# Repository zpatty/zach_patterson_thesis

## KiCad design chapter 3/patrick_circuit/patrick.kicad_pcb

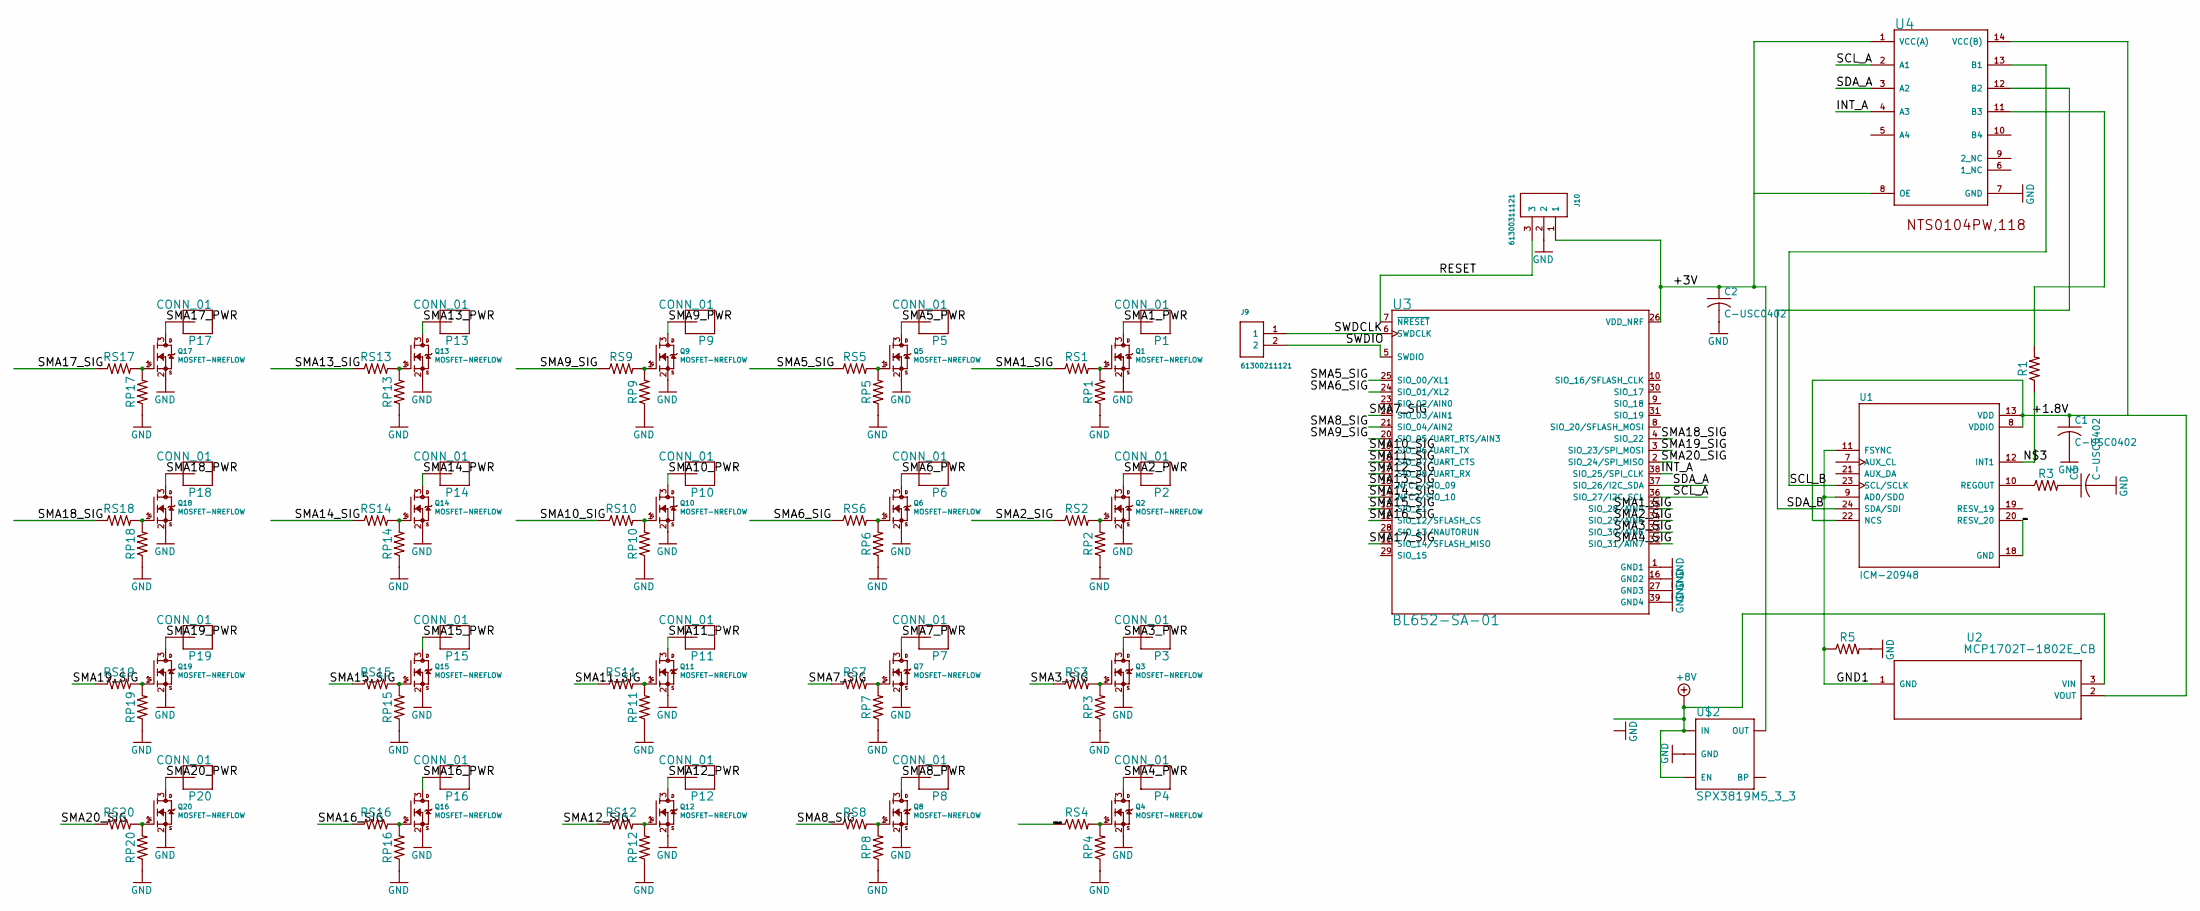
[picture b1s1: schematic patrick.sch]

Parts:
C1, C2, C3: C-USC0402; C0402
J9: 61300211121
J10: 61300311121
P1, P2, P3, P4, P5, P6, P7, P8, P9, P10, P11, P12, P13, P14, P15, P16, P17, P18, P19, P20: CONN_01; 1X01
Q1, Q2, Q3, Q4, Q5, Q6, Q7, Q8, Q9, Q10, Q11, Q12, Q13, Q14, Q15, Q16, Q17, Q18, Q19, Q20: MOSFET-NREFLOW; SOT23
R1, R3, R5: 0805
RP1, RP2, RP3, RP4, RP5, RP6, RP7, RP8, RP9, RP10, RP11, RP12, RP13, RP14, RP15, RP16, RP17, RP18, RP19, RP20: 0402
RS1, RS2, RS3, RS4, RS5, RS6, RS7, RS8, RS9, RS10, RS11, RS12, RS13, RS14, RS15, RS16, RS17, RS18, RS19, RS20: 0402
U1: ICM-20948; QFN40P300X300X105-24N
U2: MCP1702T-1802E_CB; SOT-23A_MC
U3: BL652-SA-01; XCVR_BL652-SA-01
U4: NXP_NTS0104PW,118NXP_NTS0104PW,118_0_3; NXP_NTS0104PW,118_3
U$2: SPX3819M5_3_3; SOT23-5

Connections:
+8V: U2.3 (VIN), U$2.1 (IN), U$2.3 (EN)
/+1.8V: C1.1, U1.8 (VDDIO), U1.13 (VDD), U1.22 (NCS), U2.2 (VOUT), U4.14 (VCC(B))
/+3V: C2.1, J10.1, U3.26 (VDD_NRF), U4.1 (VCC(A)), U4.8 (OE), U$2.5 (OUT)
/GND1: R5.1, U1.9 (AD0/SDO), U1.11 (FSYNC), U1.18 (GND), U1.20 (RESV_20), U2.1 (GND)
/INT_A: U3.38 (SIO_25/SPI_CLK), U4.4 (A3)
/N$3: R1.1, U1.12 (INT1)
/RESET: J10.3, U3.7 (~NRESET)
/SCL_A: U3.36 (SIO_27/I2C_SCL), U4.2 (A1)
/SCL_B: U1.23 (SCL/SCLK), U4.13 (B1)
/SDA_A: U3.37 (SIO_26/I2C_SDA), U4.3 (A2)
/SDA_B: U1.24 (SDA/SDI), U4.12 (B2)
/SMA1_PWR: P1.1, Q1.3 (D)
/SMA1_SIG: RS1.1, U3.35 (SIO_28/AIN4)
/SMA2_PWR: P2.1, Q2.3 (D)
/SMA2_SIG: RS2.1, U3.34 (SIO_29/AIN5)
/SMA3_PWR: P3.1, Q3.3 (D)
/SMA3_SIG: RS3.1, U3.33 (SIO_30/AIN6)
/SMA4_PWR: P4.1, Q4.3 (D)
/SMA4_SIG: RS4.1, U3.32 (SIO_31/AIN7)
/SMA5_PWR: P5.1, Q5.3 (D)
/SMA5_SIG: RS5.1, U3.25 (SIO_00/XL1)
/SMA6_PWR: P6.1, Q6.3 (D)
/SMA6_SIG: RS6.1, U3.24 (SIO_01/XL2)
/SMA7_PWR: P7.1, Q7.3 (D)
/SMA7_SIG: RS7.1, U3.22 (SIO_03/AIN1)
/SMA8_PWR: P8.1, Q8.3 (D)
/SMA8_SIG: RS8.1, U3.21 (SIO_04/AIN2)
/SMA9_PWR: P9.1, Q9.3 (D)
/SMA9_SIG: RS9.1, U3.20 (SIO_05/UART_RTS/AIN3)
/SMA10_PWR: P10.1, Q10.3 (D)
/SMA10_SIG: RS10.1, U3.19 (SIO_06/UART_TX)
/SMA11_PWR: P11.1, Q11.3 (D)
/SMA11_SIG: RS11.1, U3.18 (SIO_07/UART_CTS)
/SMA12_PWR: P12.1, Q12.3 (D)
/SMA12_SIG: RS12.1, U3.17 (SIO_08/UART_RX)
/SMA13_PWR: P13.1, Q13.3 (D)
/SMA13_SIG: RS13.1, U3.15 (NFC1/SIO_09)
/SMA14_PWR: P14.1, Q14.3 (D)
/SMA14_SIG: RS14.1, U3.14 (NFC2/SIO_10)
/SMA15_PWR: P15.1, Q15.3 (D)
/SMA15_SIG: RS15.1, U3.13 (SIO_11)
/SMA16_PWR: P16.1, Q16.3 (D)
/SMA16_SIG: RS16.1, U3.12 (SIO_12/SFLASH_CS)
/SMA17_PWR: P17.1, Q17.3 (D)
/SMA17_SIG: RS17.1, U3.11 (SIO_14/SFLASH_MISO)
/SMA18_PWR: P18.1, Q18.3 (D)
/SMA18_SIG: RS18.1, U3.4 (SIO_22)
/SMA19_PWR: P19.1, Q19.3 (D)
/SMA19_SIG: RS19.1, U3.3 (SIO_23/SPI_MOSI)
/SMA20_PWR: P20.1, Q20.3 (D)
/SMA20_SIG: RS20.1, U3.2 (SIO_24/SPI_MISO)
/SWDCLK: J9.1, U3.6 (SWDCLK)
/SWDIO: J9.2, U3.5 (SWDIO)
GND: C1.2, C2.2, C3.2, J10.2, Q1.2 (S), Q2.2 (S), Q3.2 (S), Q4.2 (S), Q5.2 (S), Q6.2 (S), Q7.2 (S), Q8.2 (S), Q9.2 (S), Q10.2 (S), Q11.2 (S), Q12.2 (S), Q13.2 (S), Q14.2 (S), Q15.2 (S), Q16.2 (S), Q17.2 (S), Q18.2 (S), Q19.2 (S), Q20.2 (S), R5.2, RP1.1, RP2.1, RP3.1, RP4.1, RP5.1, RP6.1, RP7.1, RP8.1, RP9.1, RP10.1, RP11.1, RP12.1, RP13.1, RP14.1, RP15.1, RP16.1, RP17.1, RP18.1, RP19.1, RP20.1, U3.1 (GND1), U3.16 (GND2), U3.27 (GND3), U3.39 (GND4), U4.7 (GND), U$2.2 (GND)
unnamed: C3.1, R3.2
unnamed: Q1.1 (G), RP1.2, RS1.2
unnamed: Q2.1 (G), RP2.2, RS2.2
unnamed: Q3.1 (G), RP3.2, RS3.2
unnamed: Q4.1 (G), RP4.2, RS4.2
unnamed: Q5.1 (G), RP5.2, RS5.2
unnamed: Q6.1 (G), RP6.2, RS6.2
unnamed: Q7.1 (G), RP7.2, RS7.2
unnamed: Q8.1 (G), RP8.2, RS8.2
unnamed: Q9.1 (G), RP9.2, RS9.2
unnamed: Q10.1 (G), RP10.2, RS10.2
unnamed: Q11.1 (G), RP11.2, RS11.2
unnamed: Q12.1 (G), RP12.2, RS12.2
unnamed: Q13.1 (G), RP13.2, RS13.2
unnamed: Q14.1 (G), RP14.2, RS14.2
unnamed: Q15.1 (G), RP15.2, RS15.2
unnamed: Q16.1 (G), RP16.2, RS16.2
unnamed: Q17.1 (G), RP17.2, RS17.2
unnamed: Q18.1 (G), RP18.2, RS18.2
unnamed: Q19.1 (G), RP19.2, RS19.2
unnamed: Q20.1 (G), RP20.2, RS20.2
unnamed: R1.2, U4.11 (B3)
unnamed: R3.1, U1.10 (REGOUT)

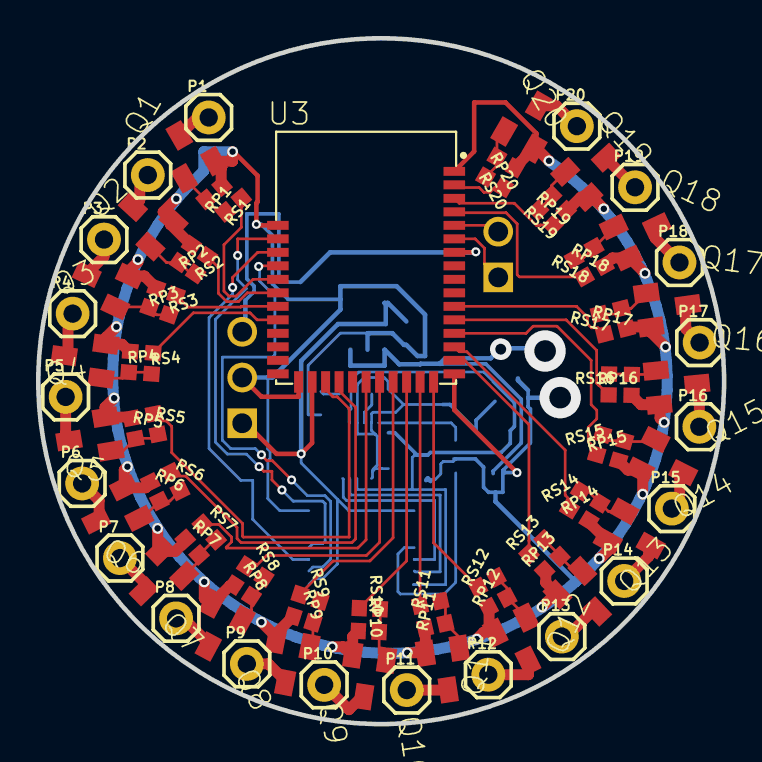
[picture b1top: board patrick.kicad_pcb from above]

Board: 2 copper layers, 38.1 x 38.1 mm, 93 parts (0 on the bottom side), 77 nets.

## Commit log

2022-07-13 adding data
